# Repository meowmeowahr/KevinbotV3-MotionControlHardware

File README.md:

# !! IMPORTANT !!

> [!CAUTION]
> Boards and schematics are not completed

# Kevinbot v3 Motion Control Hardware

tbd

## License

<p xmlns:cc="http://creativecommons.org/ns#" xmlns:dct="http://purl.org/dc/terms/"><a property="dct:title" rel="cc:attributionURL" href="https://github.com/meowmeowahr/KevinbotV3-MotionControlHardware">Kevinbot v3 Motion Control Hardware</a> by <a rel="cc:attributionURL dct:creator" property="cc:attributionName" href="https://github.com/meowmeowahr">Kevin Ahr</a> is licensed under <a href="https://creativecommons.org/licenses/by-sa/4.0/?ref=chooser-v1" target="_blank" rel="license noopener noreferrer" style="display:inline-block;">CC BY-SA 4.0</a></p> 

<br>

<a>"EE_SX1103 Footprint"</a> by <a>Prusa Research</a> is licensed under  <a href="https://creativecommons.org/licenses/by-sa/4.0/?ref=chooser-v1" target="_blank" rel="license noopener noreferrer" style="display:inline-block;">CC BY-SA 4.0</a></p> 

<a href="https://www.snapeda.com/parts/EE-SX1103/Omron%20Electronics/view-part/" target="_blank">"EE_SX1103 Cad Model"</a> by <a href="https://www.snapeda.com" target="_blank">SnapEDA</a> is licensed under <a href="https://creativecommons.org/licenses/by-sa/4.0/?ref=chooser-v1" target="_blank" rel="license noopener noreferrer" style="display:inline-block;">CC BY-SA 4.0</a></p>

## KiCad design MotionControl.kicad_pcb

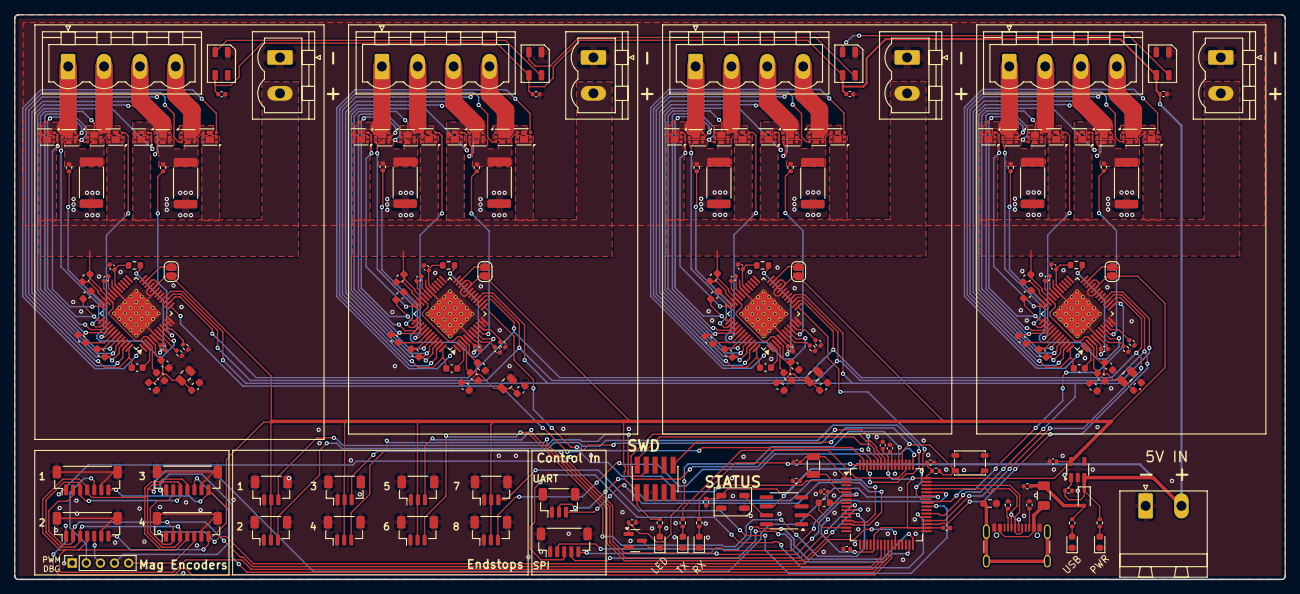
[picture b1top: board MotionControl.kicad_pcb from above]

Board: 2 copper layers, 180.0 x 80.0 mm, 191 parts (0 on the bottom side), 183 nets.

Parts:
C1, C3: 2.2uF; C_0402_1005Metric
C2, C11: 1uF; C_0402_1005Metric
C4, C5: 15pF; C_0402_1005Metric
C6, C7, C8, C9, C10, C21, C35, C49, C63, C68: 0.1uF; C_0402_1005Metric
C12, C26, C40, C54: 10uF 50V; C_0805_2012Metric
C13, C27, C41, C55: 22nF 50V; C_0402_1005Metric
C14, C15, C19, C20, C22, C23, C24, C25, C28, C29, C33, C34, C36, C37, C38, C39, C42, C43, C47, C48, C50, C51, C52, C53, C56, C57, C61, C62, C64, C65, C66, C67: 100nF 50V; C_0603_1608Metric
C16, C30, C44, C58: 470nF 10V; C_0402_1005Metric
C17, C31, C45, C59: 4.7uF 6.3V; C_0402_1005Metric
C18, C32, C46, C60: 2.2uF 25V; C_0603_1608Metric
D1, D2: LED; LED_0603_1608Metric
D3: CUS10S30; D_SOD-323
D4: Blue; LED_0603_1608Metric
D5: Green; LED_0603_1608Metric
D6: Yellow; LED_0603_1608Metric
D7, D8, D9, D10, D11: WS2812B-2020; LED_WS2812B-Mini_PLCC4_3.5x3.5mm
F1: 500mA; Fuse_1206_3216Metric
FB1: 220R; L_0603_1608Metric
J1: Screw_Terminal_01x02; PhoenixContact_MSTBA_2,5_2-G-5,08_1x02_P5.08mm_Horizontal
J2: Conn_ARM_JTAG_SWD_10; PinHeader_2x05_P1.27mm_Vertical_SMD
J3, J5, J6, J7: Screw_Terminal_01x04; PhoenixContact_MSTBVA_2,5_4-G-5,08_1x04_P5.08mm_Vertical
J4, J12, J13, J14: Conn_01x07_MountingPin; JST_SH_BM07B-SRSS-TB_1x07-1MP_P1.00mm_Vertical
J8, J9, J10, J11: Screw_Terminal_01x02; PhoenixContact_MSTBVA_2,5_2-G-5,08_1x02_P5.08mm_Vertical
J15: Conn_01x05_Pin; PinSocket_1x05_P2.00mm_Vertical
J16, J17, J19, J20, J22, J23, J25, J26, J29: Conn_01x03_MountingPin; JST_SH_BM03B-SRSS-TB_1x03-1MP_P1.00mm_Vertical
J28: Conn_01x04_MountingPin; JST_SH_BM05B-SRSS-TB_1x05-1MP_P1.00mm_Vertical
JP1: Jumper_2_Bridged; R_0603_1608Metric_Pad0.98x0.95mm_HandSolder
JP2, JP7, JP10, JP13: Jumper_2; SolderJumper-2_P1.3mm_Open_RoundedPad1.0x1.5mm
P1: USB_C_Plug_USB2.0; USB_C_Receptacle_GCT_USB4105-xx-A_16P_TopMnt_Horizontal
Q1: 2N7002; SOT-23
Q2, Q3, Q4, Q5, Q6, Q7, Q8, Q9, Q10, Q11, Q12, Q13, Q14, Q15, Q16, Q17, Q18, Q19, Q20, Q21, Q22, Q23, Q24, Q25, Q26, Q27, Q28, Q29, Q30, Q31, Q32, Q33: Q_NMOS_DGS; Diodes_DMT6016LFDF
R1: 10K; R_0402_1005Metric
R2: 10R; R_0402_1005Metric
R3, R4: 5.1K; R_0402_1005Metric
R5: 100K; R_0402_1005Metric
R6, R7: 300R; R_0402_1005Metric
R8, R9: 165R; R_0402_1005Metric
R10, R17, R24, R31: 2R; R_0603_1608Metric
R11, R12, R14, R15, R18, R19, R21, R22, R25, R26, R28, R29, R32, R33, R35, R36: 47R; R_0402_1005Metric
R13, R16, R20, R23, R27, R30, R34, R37: 50mR; R_2512_6332Metric
SW1: SW_Push; SW_SPST_PTS810
U1: ATSAMD21J18A-A; TQFP-64_10x10mm_P0.5mm
U2: AP2112K-3.3; SOT-23-5
U3, U4, U5, U6: TMC5160A-TA; TQFP-48-1EP_7x7mm_P0.5mm_EP5x5mm_ThermalVias_0.3
U7: TC4427; SOIC-8_3.9x4.9mm_P1.27mm
Y1: 32.768kHz; Crystal_SMD_3215-2Pin_3.2x1.5mm

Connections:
+3V3: C3.1, C7.1, C8.1, C9.1, C10.1, FB1.1, J2.1 (VTref), J4.7, J12.7, J13.7, J14.7, J16.2, J17.2, J19.2, J20.2, J22.2, J23.2, J25.2, J26.2, JP2.1 (A), JP7.1 (A), JP10.1 (A), JP13.1 (A), R1.1, R2.2, U1.21 (VDDIO), U1.34 (VDDIO), U1.48 (VDDIO), U1.56 (VDDIN), U2.5 (VOUT), U3.20 (VCC_IO), U3.22 (SPI_MODE), U4.20 (VCC_IO), U4.22 (SPI_MODE), U5.20 (VCC_IO), U5.22 (SPI_MODE), U6.20 (VCC_IO), U6.22 (SPI_MODE)
+5V: C2.1, C21.1, C35.1, C49.1, C63.1, C68.1, D3.1 (K), D7.1 (VDD), D8.1 (VDD), D9.1 (VDD), D10.1 (VDD), D11.1 (VDD), J1.2, R7.2, U2.1 (VIN), U2.3 (EN), U7.6 (VDD)
/D+: P1.A6 (D+), P1.B6 (D+), U1.46 (PA25)
/D-: P1.A7 (D-), P1.B7 (D-), U1.45 (PA24)
/Mag Sensors/PWM1: J13.5, J15.2
/Mag Sensors/PWM2: J14.5, J15.3
/Mag Sensors/PWM3: J4.5, J15.4
/Mag Sensors/PWM4: J12.5, J15.5
/RESETn: J2.10 (~RESET), R1.2, SW1.2, U1.52 (~RESET)
/Steppers/Stepper Unit1/BMA1: C33.1, J5.2, Q4.1 (D), Q15.3 (S), U4.40 (BMA1)
/Steppers/Stepper Unit1/BMA2: C36.2, J5.1, Q5.1 (D), Q11.3 (S), U4.37 (BMA2)
/Steppers/Stepper Unit1/BMB1: C37.1, J5.4, Q8.3 (S), Q28.1 (D), U4.48 (BMB1)
/Steppers/Stepper Unit1/BMB2: C39.2, J5.3, Q9.3 (S), Q29.1 (D), U4.45 (BMB2)
/Steppers/Stepper Unit1/CA1: C33.2, U4.42 (CA1)
/Steppers/Stepper Unit1/CA2: C36.1, U4.35 (CA2)
/Steppers/Stepper Unit1/CB1: C37.2, U4.2 (CB1)
/Steppers/Stepper Unit1/CB2: C39.1, U4.43 (CB2)
/Steppers/Stepper Unit1/HA1: Q15.2 (G), U4.41 (HA1)
/Steppers/Stepper Unit1/HA2: Q11.2 (G), U4.36 (HA2)
/Steppers/Stepper Unit1/HB1: Q8.2 (G), U4.1 (HB1)
/Steppers/Stepper Unit1/HB2: Q9.2 (G), U4.44 (HB2)
/Steppers/Stepper Unit1/LA1: Q4.2 (G), U4.39 (LA1)
/Steppers/Stepper Unit1/LA2: Q5.2 (G), U4.38 (LA2)
/Steppers/Stepper Unit1/LB1: Q28.2 (G), U4.47 (LB1)
/Steppers/Stepper Unit1/LB2: Q29.2 (G), U4.46 (LB2)
/Steppers/Stepper Unit1/LED_OUT: D8.2 (DOUT), D9.4 (DIN)
/Steppers/Stepper Unit1/SA: Q4.3 (S), Q5.3 (S), R18.1, R20.1
/Steppers/Stepper Unit1/SB: Q28.3 (S), Q29.3 (S), R21.1, R23.1
/Steppers/Stepper Unit1/SRAH: R18.2, U4.8 (SRAH)
/Steppers/Stepper Unit1/SRAL: R19.2, U4.7 (SRAL)
/Steppers/Stepper Unit1/SRBH: R21.2, U4.9 (SRBH)
/Steppers/Stepper Unit1/SRBL: R22.2, U4.10 (SRBL)
/Steppers/Stepper Unit1/VMOT: C26.1, C28.1, C29.1, C34.2, C38.2, J9.2, Q8.1 (D), Q9.1 (D), Q11.1 (D), Q15.1 (D), U4.4 (VSA), U4.33 (VS)
/Steppers/Stepper Unit2/BMA1: C47.1, J6.2, Q16.3 (S), Q18.1 (D), U5.40 (BMA1)
/Steppers/Stepper Unit2/BMA2: C50.2, J6.1, Q12.3 (S), Q19.1 (D), U5.37 (BMA2)
/Steppers/Stepper Unit2/BMB1: C51.1, J6.4, Q22.3 (S), Q30.1 (D), U5.48 (BMB1)
/Steppers/Stepper Unit2/BMB2: C53.2, J6.3, Q23.3 (S), Q31.1 (D), U5.45 (BMB2)
/Steppers/Stepper Unit2/CA1: C47.2, U5.42 (CA1)
/Steppers/Stepper Unit2/CA2: C50.1, U5.35 (CA2)
/Steppers/Stepper Unit2/CB1: C51.2, U5.2 (CB1)
/Steppers/Stepper Unit2/CB2: C53.1, U5.43 (CB2)
/Steppers/Stepper Unit2/HA1: Q16.2 (G), U5.41 (HA1)
/Steppers/Stepper Unit2/HA2: Q12.2 (G), U5.36 (HA2)
/Steppers/Stepper Unit2/HB1: Q22.2 (G), U5.1 (HB1)
/Steppers/Stepper Unit2/HB2: Q23.2 (G), U5.44 (HB2)
/Steppers/Stepper Unit2/LA1: Q18.2 (G), U5.39 (LA1)
/Steppers/Stepper Unit2/LA2: Q19.2 (G), U5.38 (LA2)
/Steppers/Stepper Unit2/LB1: Q30.2 (G), U5.47 (LB1)
/Steppers/Stepper Unit2/LB2: Q31.2 (G), U5.46 (LB2)
/Steppers/Stepper Unit2/LED_OUT: D9.2 (DOUT), D10.4 (DIN)
/Steppers/Stepper Unit2/SA: Q18.3 (S), Q19.3 (S), R25.1, R27.1
/Steppers/Stepper Unit2/SB: Q30.3 (S), Q31.3 (S), R28.1, R30.1
/Steppers/Stepper Unit2/SRAH: R25.2, U5.8 (SRAH)
/Steppers/Stepper Unit2/SRAL: R26.2, U5.7 (SRAL)
/Steppers/Stepper Unit2/SRBH: R28.2, U5.9 (SRBH)
/Steppers/Stepper Unit2/SRBL: R29.2, U5.10 (SRBL)
/Steppers/Stepper Unit2/VMOT: C40.1, C42.1, C43.1, C48.2, C52.2, J11.2, Q12.1 (D), Q16.1 (D), Q22.1 (D), Q23.1 (D), U5.4 (VSA), U5.33 (VS)
/Steppers/Stepper Unit3/BMA1: C61.1, J7.2, Q17.3 (S), Q20.1 (D), U6.40 (BMA1)
/Steppers/Stepper Unit3/BMA2: C64.2, J7.1, Q13.3 (S), Q21.1 (D), U6.37 (BMA2)
/Steppers/Stepper Unit3/BMB1: C65.1, J7.4, Q24.3 (S), Q32.1 (D), U6.48 (BMB1)
/Steppers/Stepper Unit3/BMB2: C67.2, J7.3, Q25.3 (S), Q33.1 (D), U6.45 (BMB2)
/Steppers/Stepper Unit3/CA1: C61.2, U6.42 (CA1)
/Steppers/Stepper Unit3/CA2: C64.1, U6.35 (CA2)
/Steppers/Stepper Unit3/CB1: C65.2, U6.2 (CB1)
/Steppers/Stepper Unit3/CB2: C67.1, U6.43 (CB2)
/Steppers/Stepper Unit3/HA1: Q17.2 (G), U6.41 (HA1)
/Steppers/Stepper Unit3/HA2: Q13.2 (G), U6.36 (HA2)
/Steppers/Stepper Unit3/HB1: Q24.2 (G), U6.1 (HB1)
/Steppers/Stepper Unit3/HB2: Q25.2 (G), U6.44 (HB2)
/Steppers/Stepper Unit3/LA1: Q20.2 (G), U6.39 (LA1)
/Steppers/Stepper Unit3/LA2: Q21.2 (G), U6.38 (LA2)
/Steppers/Stepper Unit3/LB1: Q32.2 (G), U6.47 (LB1)
/Steppers/Stepper Unit3/LB2: Q33.2 (G), U6.46 (LB2)
/Steppers/Stepper Unit3/SA: Q20.3 (S), Q21.3 (S), R32.1, R34.1
/Steppers/Stepper Unit3/SB: Q32.3 (S), Q33.3 (S), R35.1, R37.1
/Steppers/Stepper Unit3/SRAH: R32.2, U6.8 (SRAH)
/Steppers/Stepper Unit3/SRAL: R33.2, U6.7 (SRAL)
/Steppers/Stepper Unit3/SRBH: R35.2, U6.9 (SRBH)
/Steppers/Stepper Unit3/SRBL: R36.2, U6.10 (SRBL)
/Steppers/Stepper Unit3/VMOT: C54.1, C56.1, C57.1, C62.2, C66.2, J10.2, Q13.1 (D), Q17.1 (D), Q24.1 (D), Q25.1 (D), U6.4 (VSA), U6.33 (VS)
/Steppers/Stepper Unit/BMA1: C19.1, J3.2, Q2.1 (D), Q14.3 (S), U3.40 (BMA1)
/Steppers/Stepper Unit/BMA2: C22.2, J3.1, Q3.1 (D), Q10.3 (S), U3.37 (BMA2)
/Steppers/Stepper Unit/BMB1: C23.1, J3.4, Q6.3 (S), Q26.1 (D), U3.48 (BMB1)
/Steppers/Stepper Unit/BMB2: C25.2, J3.3, Q7.3 (S), Q27.1 (D), U3.45 (BMB2)
/Steppers/Stepper Unit/CA1: C19.2, U3.42 (CA1)
/Steppers/Stepper Unit/CA2: C22.1, U3.35 (CA2)
/Steppers/Stepper Unit/CB1: C23.2, U3.2 (CB1)
/Steppers/Stepper Unit/CB2: C25.1, U3.43 (CB2)
/Steppers/Stepper Unit/HA1: Q14.2 (G), U3.41 (HA1)
/Steppers/Stepper Unit/HA2: Q10.2 (G), U3.36 (HA2)
/Steppers/Stepper Unit/HB1: Q6.2 (G), U3.1 (HB1)
/Steppers/Stepper Unit/HB2: Q7.2 (G), U3.44 (HB2)
/Steppers/Stepper Unit/LA1: Q2.2 (G), U3.39 (LA1)
/Steppers/Stepper Unit/LA2: Q3.2 (G), U3.38 (LA2)
/Steppers/Stepper Unit/LB1: Q26.2 (G), U3.47 (LB1)
/Steppers/Stepper Unit/LB2: Q27.2 (G), U3.46 (LB2)
/Steppers/Stepper Unit/LED_OUT: D7.2 (DOUT), D8.4 (DIN)
/Steppers/Stepper Unit/SA: Q2.3 (S), Q3.3 (S), R11.1, R13.1
/Steppers/Stepper Unit/SB: Q26.3 (S), Q27.3 (S), R14.1, R16.1
/Steppers/Stepper Unit/SRAH: R11.2, U3.8 (SRAH)
/Steppers/Stepper Unit/SRAL: R12.2, U3.7 (SRAL)
/Steppers/Stepper Unit/SRBH: R14.2, U3.9 (SRBH)
/Steppers/Stepper Unit/SRBL: R15.2, U3.10 (SRBL)
/Steppers/Stepper Unit/VMOT: C12.1, C14.1, C15.1, C20.2, C24.2, J8.2, Q6.1 (D), Q7.1 (D), Q10.1 (D), Q14.1 (D), U3.4 (VSA), U3.33 (VS)
GND: C1.2, C2.2, C3.2, C4.1, C5.1, C6.2, C7.2, C8.2, C9.2, C10.2, C11.2, C12.2, C14.2, C16.1, C17.1, C18.2, C20.1, C21.2, C24.1, C26.2, C28.2, C30.1, C31.1, C32.2, C34.1, C35.2, C38.1, C40.2, C42.2, C44.1, C45.1, C46.2, C48.1, C49.2, C52.1, C54.2, C56.2, C58.1, C59.1, C60.2, C62.1, C63.2, C66.1, C68.2, D1.1 (K), D2.1 (K), D5.1 (K), D6.1 (K), D7.3 (VSS), D8.3 (VSS), D9.3 (VSS), D10.3 (VSS), D11.3 (VSS), J1.1, J2.3 (GND), J2.5 (GND), J4.6, J4.MP (MountPin), J8.1, J9.1, J10.1, J11.1, J12.6, J12.MP (MountPin), J13.6, J13.MP (MountPin), J14.6, J14.MP (MountPin), J15.1, J16.1, J16.MP (MountPin), J17.1, J17.MP (MountPin), J19.1, J19.MP (MountPin), J20.1, J20.MP (MountPin), J22.1, J22.MP (MountPin), J23.1, J23.MP (MountPin), J25.1, J25.MP (MountPin), J26.1, J26.MP (MountPin), J28.1, J28.MP (MountPin), J29.1, J29.MP (MountPin), JP1.2 (B), P1.A1 (GND), P1.A12 (GND), P1.B1 (GND), P1.B12 (GND), Q1.2 (S), R3.2, R4.2, R5.1, R12.1, R13.2, R15.1, R16.2, R19.1, R20.2, R22.1, R23.2, R26.1, R27.2, R29.1, R30.2, R33.1, R34.2, R36.1, R37.2, SW1.1, U1.7 (GNDANA), U1.22 (GND), U1.33 (GND), U1.47 (GND), U1.54 (GND), U2.2 (GND), U3.6 (GNDA), U3.11 (TST_MODE), U3.12 (CLK), U3.19 (GNDD), U3.21 (SD_MODE), U3.30 (GNDD), U3.49 (EP), U4.6 (GNDA), U4.11 (TST_MODE), U4.12 (CLK), U4.19 (GNDD), U4.21 (SD_MODE), U4.30 (GNDD), U4.49 (EP), U5.6 (GNDA), U5.11 (TST_MODE), U5.12 (CLK), U5.19 (GNDD), U5.21 (SD_MODE), U5.30 (GNDD), U5.49 (EP), U6.6 (GNDA), U6.11 (TST_MODE), U6.12 (CLK), U6.19 (GNDD), U6.21 (SD_MODE), U6.30 (GNDD), U6.49 (EP), U7.3 (GND)
unnamed: D1.2 (A), R6.1
unnamed: D2.2 (A), R7.1
unnamed: D4.2 (A), R2.1
unnamed: D4.1 (K), Q1.3 (D)
unnamed: D5.2 (A), R8.1
unnamed: D6.2 (A), R9.1
unnamed: D11.4 (DIN), U7.7 (OUTA)
unnamed: F1.1, P1.A4 (VBUS), P1.A9 (VBUS), P1.B4 (VBUS), P1.B9 (VBUS)
unnamed: JP1.1 (A), P1.S1 (SHIELD)
unnamed: JP2.2 (B), U3.23 (ENCB/DCEN/CFG4)
unnamed: JP7.2 (B), U4.23 (ENCB/DCEN/CFG4)
unnamed: JP10.2 (B), U5.23 (ENCB/DCEN/CFG4)
unnamed: JP13.2 (B), U6.23 (ENCB/DCEN/CFG4)
unnamed: P1.A5 (CC1), R3.1
unnamed: P1.B5 (CC2), R4.1
unnamed: C4.2, U1.1 (PA00), Y1.1
unnamed: C5.2, U1.2 (PA01), Y1.2
unnamed: C6.1, FB1.2, U1.8 (VDDANA)
unnamed: C11.1, U1.55 (VDDCORE)
unnamed: C17.2, R10.2, U3.5 (5VOUT)
unnamed: C18.1, U3.3 (12VOUT)
unnamed: C13.2, U3.32 (CPI)
unnamed: C13.1, U3.31 (CPO)
unnamed: C16.2, R10.1, U3.29 (VCC)
unnamed: C15.2, U3.34 (VCP)
unnamed: C31.2, R17.2, U4.5 (5VOUT)
unnamed: C32.1, U4.3 (12VOUT)
unnamed: C27.2, U4.32 (CPI)
unnamed: C27.1, U4.31 (CPO)
unnamed: C30.2, R17.1, U4.29 (VCC)
unnamed: C29.2, U4.34 (VCP)
unnamed: C45.2, R24.2, U5.5 (5VOUT)
unnamed: C46.1, U5.3 (12VOUT)
unnamed: C41.2, U5.32 (CPI)
unnamed: C41.1, U5.31 (CPO)
unnamed: C44.2, R24.1, U5.29 (VCC)
unnamed: C43.2, U5.34 (VCP)
unnamed: C59.2, R31.2, U6.5 (5VOUT)
unnamed: C60.1, U6.3 (12VOUT)
unnamed: C55.2, U6.32 (CPI)
unnamed: C55.1, U6.31 (CPO)
unnamed: C58.2, R31.1, U6.29 (VCC)
unnamed: C57.2, U6.34 (VCP)
PA04_MASTER_TX: J29.2, U1.13 (PA04)
PA05_MASTER_RX: J29.3, U1.14 (PA05)
PA06_NEOPIX: U1.15 (PA06), U7.2 (INA)
PA14_MASTER_SCK: J28.4, U1.31 (PA14)
PA15_MASTER_MOSI: J28.2, U1.32 (PA15)
PA16_TMC_MOSI: U1.35 (PA16), U3.15 (SDI/CFG1), U4.15 (SDI/CFG1), U5.15 (SDI/CFG1), U6.15 (SDI/CFG1)
PA17_TMC_SCK: U1.36 (PA17), U3.14 (SCK/CFG2), U4.14 (SCK/CFG2), U5.14 (SCK/CFG2), U6.14 (SCK/CFG2)
PA18_MAG_CSn4: J12.1, U1.27 (PB14)
PA18_MASTER_MISO: J28.3, U1.37 (PA18)
PA19_TMC_MISO: U1.38 (PA19), U3.16 (SDO/CFG0), U4.16 (SDO/CFG0), U5.16 (SDO/CFG0), U6.16 (SDO/CFG0)
PA20_TMC_CSn1: U1.41 (PA20), U3.13 (~CS/CFG3)
PA21_TMC_CSn2: U1.42 (PA21), U4.13 (~CS/CFG3)
PA22_MAG_MISO: J4.3, J12.3, J13.3, J14.3, U1.43 (PA22)
PA23_MASTER_CS: J28.5, U1.44 (PA23)
PA27_TX_LED: R8.2, U1.51 (PA27)
PA28_LED: Q1.1 (G), R5.2, U1.53 (PA28)
PB00_ES1: J16.3, U1.61 (PB00)
PB01_ES2: J17.3, U1.62 (PB01)
PB02_TMC_CSn3: U1.63 (PB02), U5.13 (~CS/CFG3)
PB03_RX_LED: R9.2, U1.64 (PB03)
PB04_TMC_CSn4: U1.5 (PB04), U6.13 (~CS/CFG3)
PB05_ES3: J19.3, U1.6 (PB05)
PB06_ES4: J20.3, U1.9 (PB06)
PB07_ES5: J22.3, U1.10 (PB07)
PB08_ES6: J23.3, U1.11 (PB08)
PB10_MAG_MOSI: J4.2, J12.2, J13.2, J14.2, U1.23 (PB10)
PB11_MAG_SCK: J4.4, J12.4, J13.4, J14.4, U1.24 (PB11)
PB12_MAG_CSn3: J4.1, U1.25 (PB12)
PB13_MAG_CSn2: J14.1, U1.26 (PB13)
PB17_ES8: J25.3, U1.40 (PB17)
PB22_ES8: J26.3, U1.49 (PB22)
PB30_MAG_CSn1: J13.1, U1.59 (PB30)
SWDCLK: J2.4 (SWCLK/TCK), U1.57 (PA30)
SWDIO: J2.2 (SWDIO/TMS), U1.58 (PA31)
VBUS: C1.1, D3.2 (A), F1.2, R6.2

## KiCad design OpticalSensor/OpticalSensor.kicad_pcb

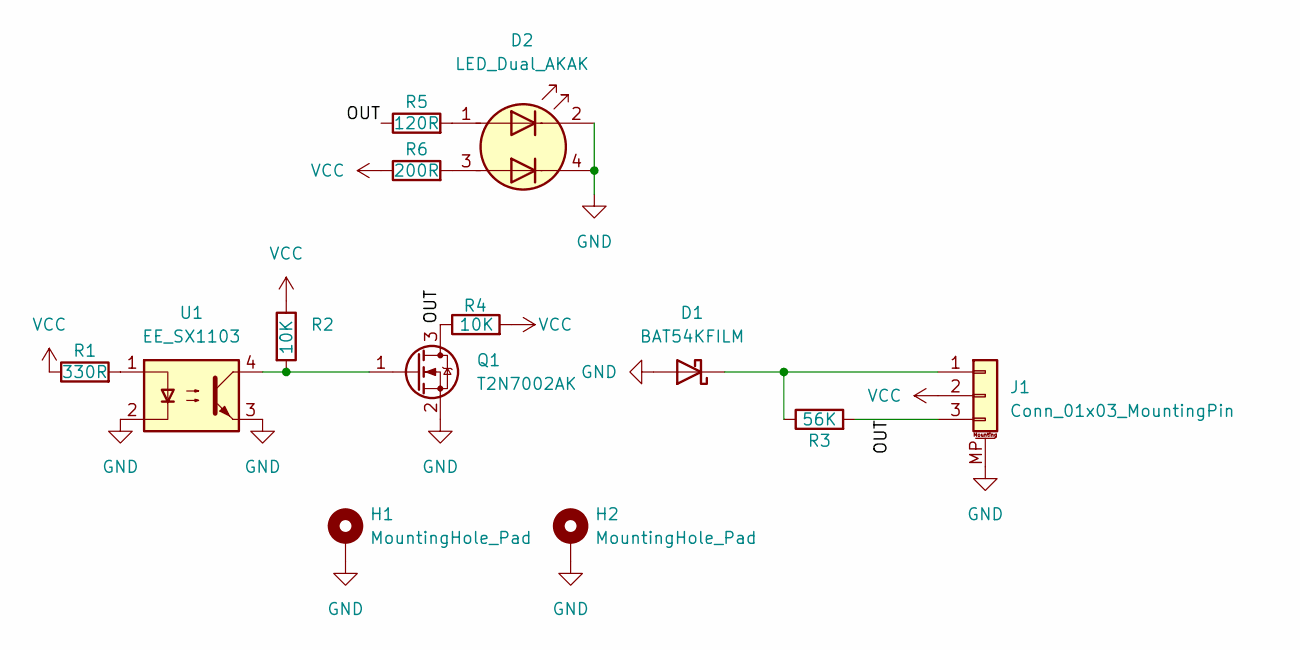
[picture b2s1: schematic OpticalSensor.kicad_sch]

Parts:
D1: BAT54KFILM; D_SOD-523; Part BAT54KFILM; LCSC C283259
D2: LED_Dual_AKAK; QBLP600-RIB; Part QBLP600-RIB
H1, H2: MountingHole_Pad; MountingHole_3.2mm_M3_DIN965_Pad_TopBottom
J1: Conn_01x03_MountingPin; JST_SH_SM03B-SRSS-TB_1x03-1MP_P1.00mm_Horizontal; Part SM03B-SRSS-TB; LCSC C160403
Q1: T2N7002AK; SOT-23; Part T2N7002AK,LM; LCSC C5224226
R1: 330R; R_0402_1005Metric; Part ERJ-2RKF3300X; LCSC C2759496
R2, R4: 10K; R_0402_1005Metric; Part ERJ-2RKF1002X; LCSC C414854
R3: 56K; R_0402_1005Metric; Part ERJ-2RKF5602X; LCSC C131604
R5: 120R; R_0402_1005Metric; Partq ERJ-2RKF1200X; LCSC C159875
R6: 200R; R_0402_1005Metric; Part ERJ-2RKF2000X; LCSC C2759465
U1: EE_SX1103; IR-EE-SX1103; Part EE-SX1103; LCSC C2931100

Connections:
/OUT: J1.3, Q1.3 (D), R3.2, R4.1, R5.1
GND: D1.2 (A), D2.2 (K1), D2.4 (K2), H1.1, H2.1, J1.MP (MountPin), Q1.2 (S), U1.2, U1.3
unnamed: D1.1 (K), J1.1, R3.1
unnamed: D2.1 (A1), R5.2
unnamed: D2.3 (A2), R6.2
unnamed: Q1.1 (G), R2.2, U1.4
unnamed: R1.2, U1.1
VCC: J1.2, R1.1, R2.1, R4.2, R6.1

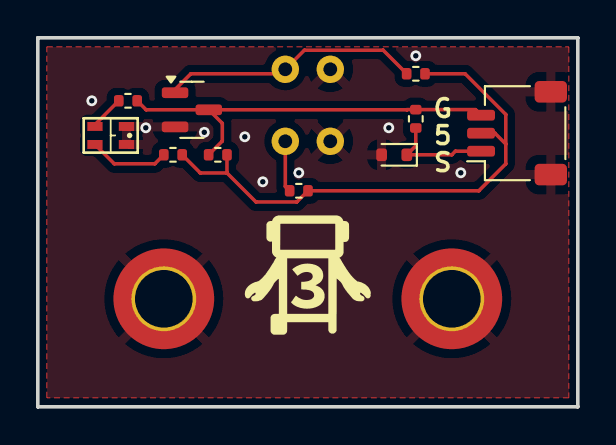
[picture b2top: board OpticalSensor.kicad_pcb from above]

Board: 2 copper layers, 30.0 x 20.5 mm, 13 parts (1 on the bottom side), 8 nets.

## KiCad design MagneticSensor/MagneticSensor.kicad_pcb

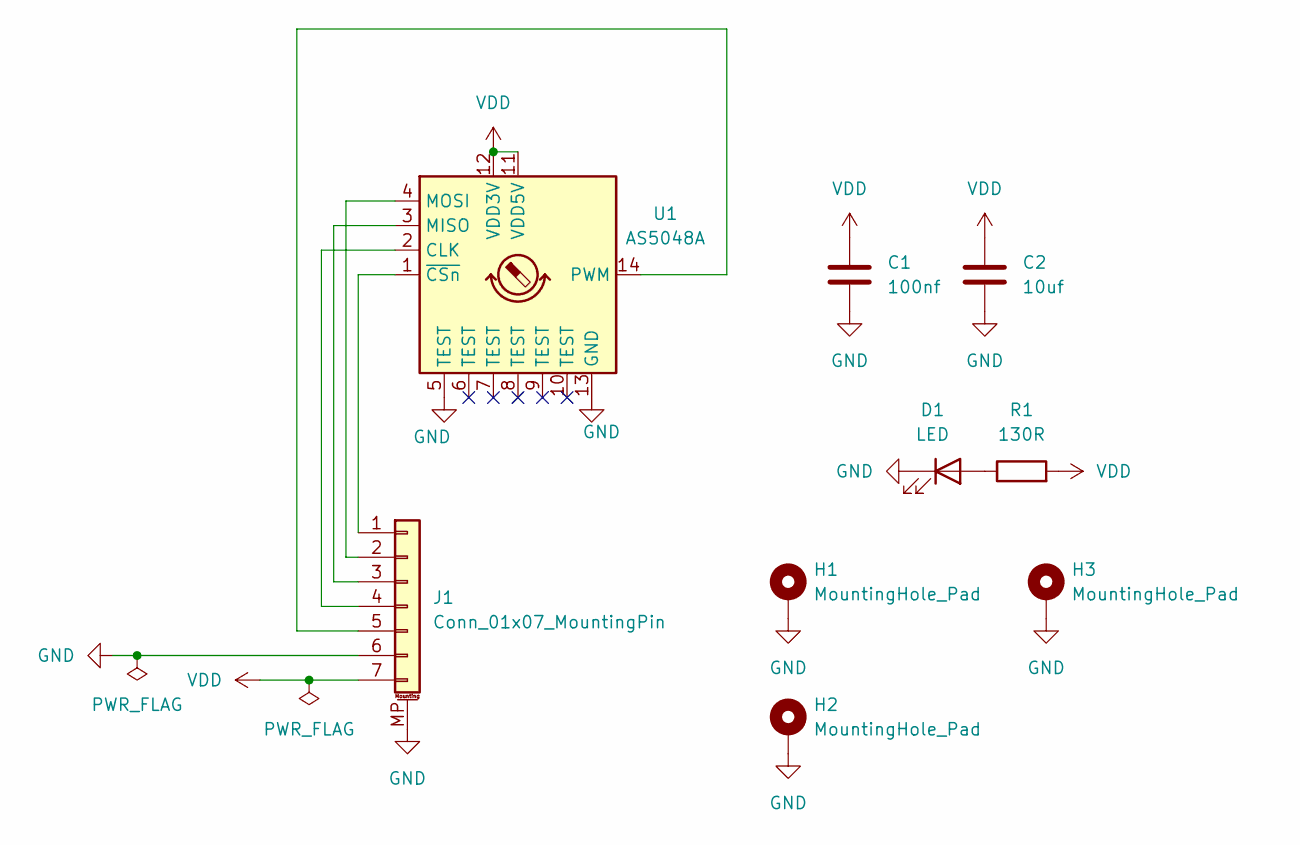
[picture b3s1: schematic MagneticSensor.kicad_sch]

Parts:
C1: 100nf; C_0402_1005Metric; Part CL05B104KP5NNNC
C2: 10uf; C_0603_1608Metric; Part CL10A106MQ8NNNC
D1: LED; LED_0603_1608Metric; Part 150060RS75000
H1, H2, H3: MountingHole_Pad; MountingHole_3.2mm_M3_ISO14580_Pad
J1: Conn_01x07_MountingPin; JST_SH_SM07B-SRSS-TB_1x07-1MP_P1.00mm_Horizontal; Part SM07B-SRSS-TB
R1: 130R; R_0402_1005Metric; Part ERJ-2RKF1300X
U1: AS5048A; TSSOP-14_4.4x5mm_P0.65mm; Part AS5048A-HTSP-500

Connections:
GND: C1.2, C2.2, D1.1 (K), H1.1, H2.1, H3.1, J1.6, J1.MP (MountPin), U1.5 (TEST), U1.13 (GND)
unnamed: D1.2 (A), R1.1
unnamed: J1.1, U1.1 (~CSn)
unnamed: J1.2, U1.4 (MOSI)
unnamed: J1.3, U1.3 (MISO)
unnamed: J1.4, U1.2 (CLK)
unnamed: J1.5, U1.14 (PWM)
VDD: C1.1, C2.1, J1.7, R1.2, U1.11 (VDD5V), U1.12 (VDD3V)

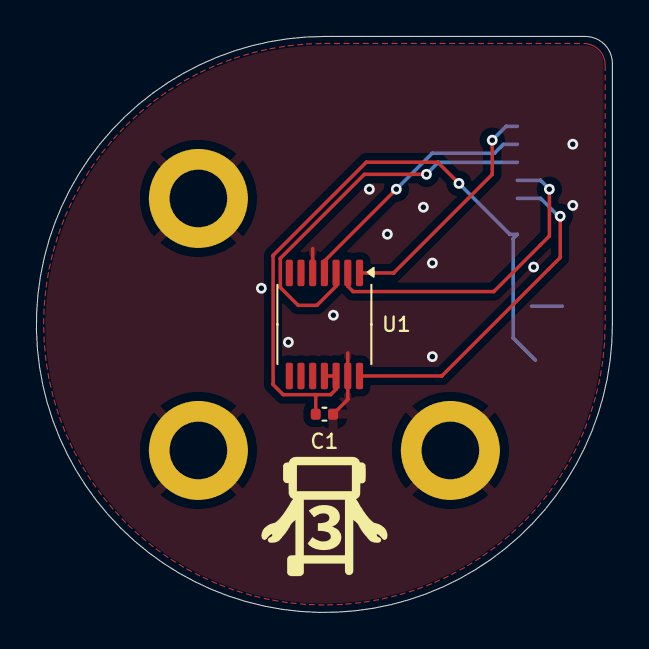
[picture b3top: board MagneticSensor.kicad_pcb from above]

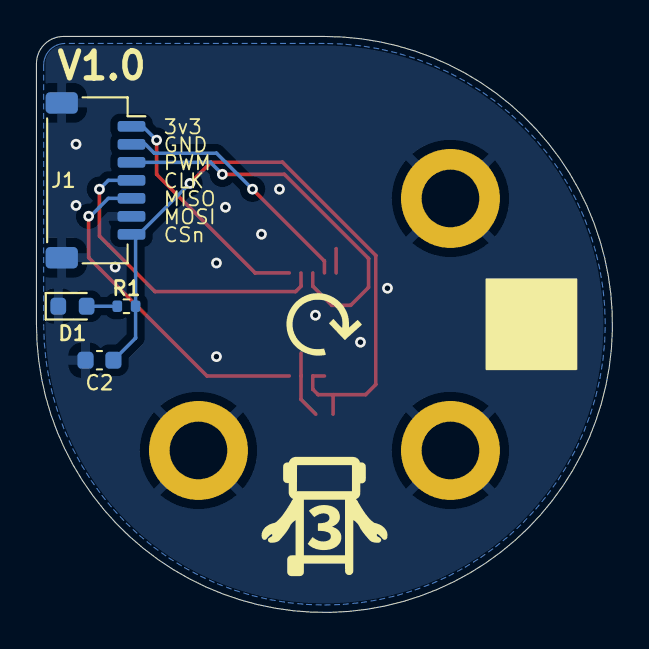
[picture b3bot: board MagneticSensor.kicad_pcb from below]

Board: 2 copper layers, 32.0 x 32.0 mm, 9 parts (4 on the bottom side), 8 nets.

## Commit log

2024-12-20 Blank kicad project
2024-12-20 Blank OpticalSensor project
2024-12-20 Optical sensor board component positioning
    Add EE_SX1103 Optical sensor
    Add JST Connector
    Add Silkscreen logo, JLCPCB QR Placement
2024-12-21 Initial board
    Added complementary components
    Board should be functional
2024-12-21 Power and status led
2024-12-21 LCSC component part numbers, board resize
2024-12-21 Led footprint updates
2024-12-21 Remove incompatible lcsc id
2024-12-21 DigiKey Part references
2024-12-23 Begin work on mag encoder
2024-12-23 Initial mag encoder board
2024-12-23 mag: move version text
2024-12-25 Begin work on SAMD21 motion controller
2024-12-25 tx, rx leds
2024-12-26 Stepper unit
    Made first revision for stepper unit
    Contains TMC5160, Status LED, FETs, and complementary comps
    Will be x4 later
2024-12-26 x4 stepper units
2024-12-27 Lots of work
2024-12-28 first stepper unit
2024-12-28 stepper unit 2 and 3, begin work on unit 4
2024-12-28 Add stepper unit 4
2024-12-30 lots of changes for mcu
    more routed connections
2025-01-01 Route swd header
2025-01-03 Begin spi routing
2025-01-03 Route tmc spi busses, cs
2025-01-03 Updated footprints, digikey parts
2025-01-09 Begin addition of mag sensor conns
2025-01-09 silkscreen changes, start routing spi
2025-01-09 fix optical sensor routing
2025-01-09 begin work on optical inputs, finish mag sensors
2025-01-10 cs routing changes, endstop stuff
2025-01-10 route all endstops
2025-01-10 add spi master connector
2025-01-10 add spi cs pin, remove center endstop support
2025-01-10 add blank docs
2025-01-10 docs and ibom github action testing
2025-01-10 Add Dockerfile
2025-01-10 try to fix bom generator
2025-01-10 fake x display for bom generator
2025-01-10 maybe fix x display
2025-01-10 Fix background Xvfb command
2025-01-10 Use kicad 8.0 in actions
2025-01-10 oops
2025-01-10 fix repo again
2025-01-10 Update Dockerfile
2025-01-10 Fix tzdata in docker
2025-01-10 Update workflow dispatcher
2025-01-10 fix timezone again
2025-01-10 no browser after ibom generate
2025-01-10 Disable actions fail-fast
2025-01-10 segfault trap
2025-01-10 fix paths in action
2025-01-10 misc fixes
2025-01-11 Add all 3 board iboms
2025-01-11 Fix error in action
2025-01-11 maybe get action working again
2025-01-11 fix x display in action
2025-01-11 add iboms to docs
2025-01-11 fix docs.yaml formatting
2025-01-11 better action debug
2025-01-11 another action fix attempt
2025-01-11 Update ibom settings
2025-01-11 more testing
2025-01-11 Attempt netlist generate on action
2025-01-11 whoops
2025-01-11 Another attempt at fixing netlist generation
2025-01-11 docs: Add ibom visit links
